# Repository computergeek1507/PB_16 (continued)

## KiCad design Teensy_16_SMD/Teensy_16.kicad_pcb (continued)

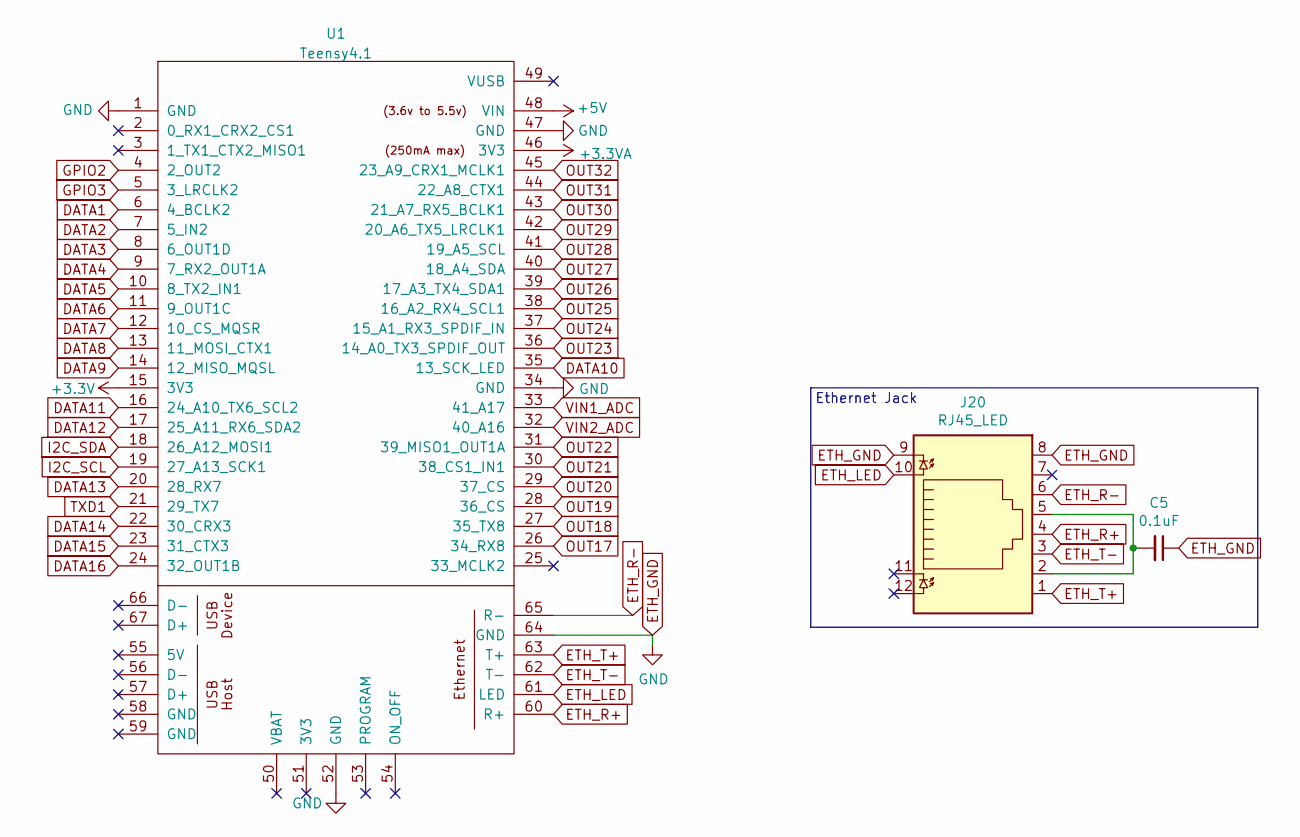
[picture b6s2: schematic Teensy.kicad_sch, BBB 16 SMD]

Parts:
C5: 0.1uF; C_0805_2012Metric; LCSC C49678
J20: RJ45_LED; RJ45_Cetus_J1B1211CCD_Horizontal
U1: Teensy4.1; Teensy41

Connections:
+3.3VA: U1.46 (3V3); also elsewhere on the board
+3V3: U1.15 (3V3); also elsewhere on the board
+5V: U1.48 (VIN); also elsewhere on the board
DATA1: U1.6 (4_BCLK2); also elsewhere on the board
DATA2: U1.7 (5_IN2); also elsewhere on the board
DATA3: U1.8 (6_OUT1D); also elsewhere on the board
DATA4: U1.9 (7_RX2_OUT1A); also elsewhere on the board
DATA5: U1.10 (8_TX2_IN1); also elsewhere on the board
DATA6: U1.11 (9_OUT1C); also elsewhere on the board
DATA7: U1.12 (10_CS_MQSR); also elsewhere on the board
DATA8: U1.13 (11_MOSI_CTX1); also elsewhere on the board
DATA9: U1.14 (12_MISO_MQSL); also elsewhere on the board
DATA10: U1.35 (13_SCK_LED); also elsewhere on the board
DATA11: U1.16 (24_A10_TX6_SCL2); also elsewhere on the board
DATA12: U1.17 (25_A11_RX6_SDA2); also elsewhere on the board
DATA13: U1.20 (28_RX7); also elsewhere on the board
DATA14: U1.22 (30_CRX3); also elsewhere on the board
DATA15: U1.23 (31_CTX3); also elsewhere on the board
DATA16: U1.24 (32_OUT1B); also elsewhere on the board
ETH_GND: C5.1, J20.8, J20.9, U1.1 (GND), U1.34 (GND), U1.47 (GND), U1.52 (GND), U1.64 (GND); also elsewhere on the board
ETH_LED: J20.10, U1.61 (LED)
ETH_R+: J20.4, U1.60 (R+)
ETH_R-: J20.6, U1.65 (R-)
ETH_T+: J20.1, U1.63 (T+)
ETH_T-: J20.3, U1.62 (T-)
GPIO2: U1.4 (2_OUT2); also elsewhere on the board
GPIO3: U1.5 (3_LRCLK2); also elsewhere on the board
I2C_SCL: U1.19 (27_A13_SCK1); also elsewhere on the board
I2C_SDA: U1.18 (26_A12_MOSI1); also elsewhere on the board
unnamed: C5.2, J20.2, J20.5
OUT17: U1.26 (34_RX8); also elsewhere on the board
OUT18: U1.27 (35_TX8); also elsewhere on the board
OUT19: U1.28 (36_CS); also elsewhere on the board
OUT20: U1.29 (37_CS); also elsewhere on the board
OUT21: U1.30 (38_CS1_IN1); also elsewhere on the board
OUT22: U1.31 (39_MISO1_OUT1A); also elsewhere on the board
OUT23: U1.36 (14_A0_TX3_SPDIF_OUT); also elsewhere on the board
OUT24: U1.37 (15_A1_RX3_SPDIF_IN); also elsewhere on the board
OUT25: U1.38 (16_A2_RX4_SCL1); also elsewhere on the board
OUT26: U1.39 (17_A3_TX4_SDA1); also elsewhere on the board
OUT27: U1.40 (18_A4_SDA); also elsewhere on the board
OUT28: U1.41 (19_A5_SCL); also elsewhere on the board
OUT29: U1.42 (20_A6_TX5_LRCLK1); also elsewhere on the board
OUT30: U1.43 (21_A7_RX5_BCLK1); also elsewhere on the board
OUT31: U1.44 (22_A8_CTX1); also elsewhere on the board
OUT32: U1.45 (23_A9_CRX1_MCLK1); also elsewhere on the board
TXD1: U1.21 (29_TX7); also elsewhere on the board
VIN1_ADC: U1.33 (41_A17); also elsewhere on the board
VIN2_ADC: U1.32 (40_A16); also elsewhere on the board

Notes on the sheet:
Ethernet Jack

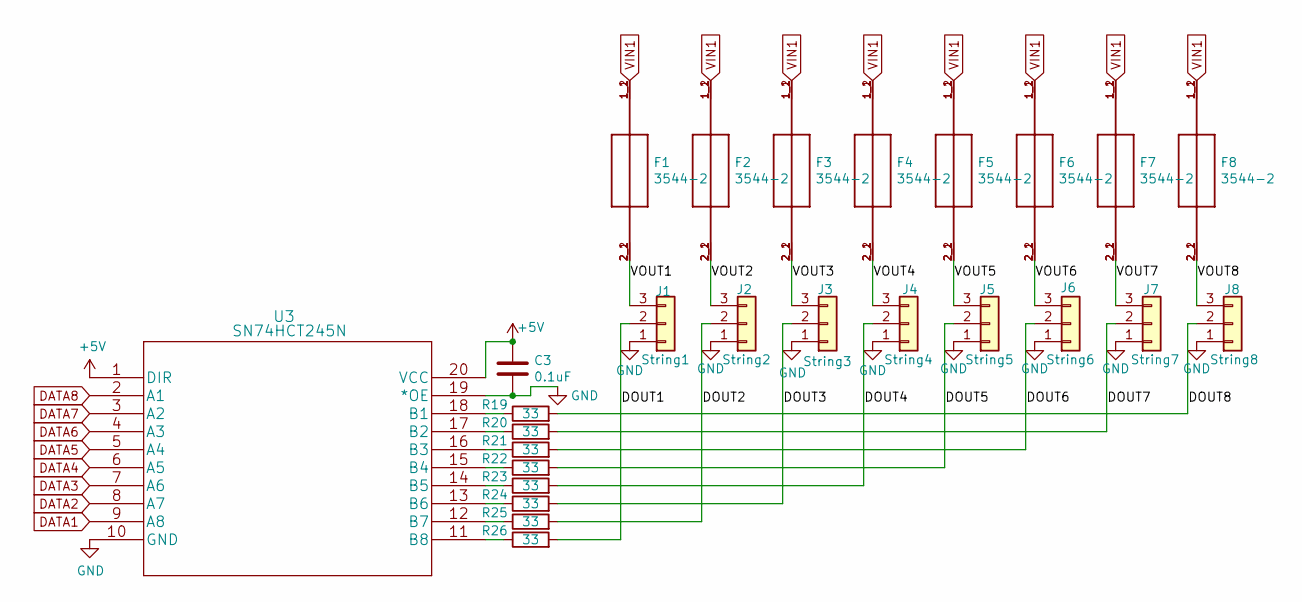
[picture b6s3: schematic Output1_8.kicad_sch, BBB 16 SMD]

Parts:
C3: 0.1uF; C_0603_1608Metric_Pad1.08x0.95mm_HandSolder; MPN CL10B104KB8NNWC; Digi-Key_PN 1276-1935-2-ND
F1, F2, F3, F4, F5, F6, F7, F8: 3544-2; FUSE_3544-2; MPN 3544-2; Digi-Key_PN 36-3544-2-ND
J1: String1; PhoenixContact_MCV_1,5_3-G-3.5_1x03_P3.50mm_Vertical; MPN 1843619/OSTTJ0311530; Digi-Key_PN 277-5737-ND/ED10555-ND
J2: String2; PhoenixContact_MCV_1,5_3-G-3.5_1x03_P3.50mm_Vertical; MPN 1843619/OSTTJ0311530; Digi-Key_PN 277-5737-ND/ED10555-ND
J3: String3; PhoenixContact_MCV_1,5_3-G-3.5_1x03_P3.50mm_Vertical; MPN 1843619/OSTTJ0311530; Digi-Key_PN 277-5737-ND/ED10555-ND
J4: String4; PhoenixContact_MCV_1,5_3-G-3.5_1x03_P3.50mm_Vertical; MPN 1843619/OSTTJ0311530; Digi-Key_PN 277-5737-ND/ED10555-ND
J5: String5; PhoenixContact_MCV_1,5_3-G-3.5_1x03_P3.50mm_Vertical; MPN 1843619/OSTTJ0311530; Digi-Key_PN 277-5737-ND/ED10555-ND
J6: String6; PhoenixContact_MCV_1,5_3-G-3.5_1x03_P3.50mm_Vertical; MPN 1843619/OSTTJ0311530; Digi-Key_PN 277-5737-ND/ED10555-ND
J7: String7; PhoenixContact_MCV_1,5_3-G-3.5_1x03_P3.50mm_Vertical; MPN 1843619/OSTTJ0311530; Digi-Key_PN 277-5737-ND/ED10555-ND
J8: String8; PhoenixContact_MCV_1,5_3-G-3.5_1x03_P3.50mm_Vertical; MPN 1843619/OSTTJ0311530; Digi-Key_PN 277-5737-ND/ED10555-ND
R19, R20, R21, R22, R23, R24, R25, R26: 33; R_0603_1608Metric_Pad0.98x0.95mm_HandSolder; MPN CN34J330CT; LCSC C23140
U3: SN74HCT245N; SN74HCT245NSR; MPN SN74HC245PWR; Digi-Key_PN 296-8279-1-ND

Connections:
+5V: C3.1, U3.1 (DIR), U3.20 (VCC); also elsewhere on the board
/Output 1-8/DOUT1: J1.2, R26.2
/Output 1-8/DOUT2: J2.2, R25.2
/Output 1-8/DOUT3: J3.2, R24.2
/Output 1-8/DOUT4: J4.2, R23.2
/Output 1-8/DOUT5: J5.2, R22.2
/Output 1-8/DOUT6: J6.2, R21.2
/Output 1-8/DOUT7: J7.2, R20.2
/Output 1-8/DOUT8: J8.2, R19.2
/Output 1-8/VOUT1: F1.2_1 (2), F1.2_2 (2), J1.3
/Output 1-8/VOUT2: F2.2_1 (2), F2.2_2 (2), J2.3
/Output 1-8/VOUT3: F3.2_1 (2), F3.2_2 (2), J3.3
/Output 1-8/VOUT4: F4.2_1 (2), F4.2_2 (2), J4.3
/Output 1-8/VOUT5: F5.2_1 (2), F5.2_2 (2), J5.3
/Output 1-8/VOUT6: F6.2_1 (2), F6.2_2 (2), J6.3
/Output 1-8/VOUT7: F7.2_1 (2), F7.2_2 (2), J7.3
/Output 1-8/VOUT8: F8.2_1 (2), F8.2_2 (2), J8.3
DATA1: U3.9 (A8); also elsewhere on the board
DATA2: U3.8 (A7); also elsewhere on the board
DATA3: U3.7 (A6); also elsewhere on the board
DATA4: U3.6 (A5); also elsewhere on the board
DATA5: U3.5 (A4); also elsewhere on the board
DATA6: U3.4 (A3); also elsewhere on the board
DATA7: U3.3 (A2); also elsewhere on the board
DATA8: U3.2 (A1); also elsewhere on the board
ETH_GND: C3.2, J1.1, J2.1, J3.1, J4.1, J5.1, J6.1, J7.1, J8.1, U3.10 (GND), U3.19 (*OE); also elsewhere on the board
unnamed: R19.1, U3.18 (B1)
unnamed: R20.1, U3.17 (B2)
unnamed: R21.1, U3.16 (B3)
unnamed: R22.1, U3.15 (B4)
unnamed: R23.1, U3.14 (B5)
unnamed: R24.1, U3.13 (B6)
unnamed: R25.1, U3.12 (B7)
unnamed: R26.1, U3.11 (B8)
VIN1: F1.1_1 (1), F1.1_2 (1), F2.1_1 (1), F2.1_2 (1), F3.1_1 (1), F3.1_2 (1), F4.1_1 (1), F4.1_2 (1), F5.1_1 (1), F5.1_2 (1), F6.1_1 (1), F6.1_2 (1), F7.1_1 (1), F7.1_2 (1), F8.1_1 (1), F8.1_2 (1); also elsewhere on the board

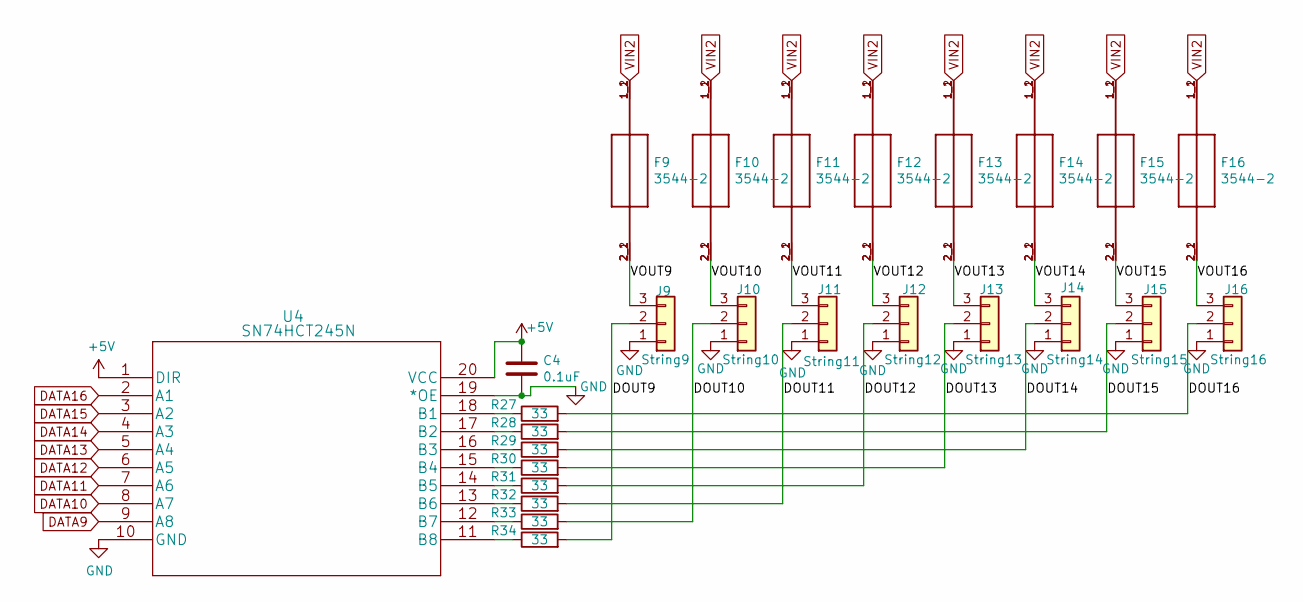
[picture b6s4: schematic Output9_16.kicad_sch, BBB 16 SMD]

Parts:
C4: 0.1uF; C_0603_1608Metric_Pad1.08x0.95mm_HandSolder; MPN CL10B104KB8NNWC; Digi-Key_PN 1276-1935-2-ND
F9, F10, F11, F12, F13, F14, F15, F16: 3544-2; FUSE_3544-2; MPN 3544-2; Digi-Key_PN 36-3544-2-ND
J9: String9; PhoenixContact_MCV_1,5_3-G-3.5_1x03_P3.50mm_Vertical; MPN 1843619/OSTTJ0311530; Digi-Key_PN 277-5737-ND/ED10555-ND
J10: String10; PhoenixContact_MCV_1,5_3-G-3.5_1x03_P3.50mm_Vertical; MPN 1843619/OSTTJ0311530; Digi-Key_PN 277-5737-ND/ED10555-ND
J11: String11; PhoenixContact_MCV_1,5_3-G-3.5_1x03_P3.50mm_Vertical; MPN 1843619/OSTTJ0311530; Digi-Key_PN 277-5737-ND/ED10555-ND
J12: String12; PhoenixContact_MCV_1,5_3-G-3.5_1x03_P3.50mm_Vertical; MPN 1843619/OSTTJ0311530; Digi-Key_PN 277-5737-ND/ED10555-ND
J13: String13; PhoenixContact_MCV_1,5_3-G-3.5_1x03_P3.50mm_Vertical; MPN 1843619/OSTTJ0311530; Digi-Key_PN 277-5737-ND/ED10555-ND
J14: String14; PhoenixContact_MCV_1,5_3-G-3.5_1x03_P3.50mm_Vertical; MPN 1843619/OSTTJ0311530; Digi-Key_PN 277-5737-ND/ED10555-ND
J15: String15; PhoenixContact_MCV_1,5_3-G-3.5_1x03_P3.50mm_Vertical; MPN 1843619/OSTTJ0311530; Digi-Key_PN 277-5737-ND/ED10555-ND
J16: String16; PhoenixContact_MCV_1,5_3-G-3.5_1x03_P3.50mm_Vertical; MPN 1843619/OSTTJ0311530; Digi-Key_PN 277-5737-ND/ED10555-ND
R27, R28, R29, R30, R31, R32, R33, R34: 33; R_0603_1608Metric_Pad0.98x0.95mm_HandSolder; MPN CN34J330CT; LCSC C23140
U4: SN74HCT245N; SN74HCT245NSR; MPN SN74HC245PWR; Digi-Key_PN 296-8279-1-ND

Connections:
+5V: C4.1, U4.1 (DIR), U4.20 (VCC); also elsewhere on the board
/Output 9-16/DOUT9: J9.2, R34.2
/Output 9-16/DOUT10: J10.2, R33.2
/Output 9-16/DOUT11: J11.2, R32.2
/Output 9-16/DOUT12: J12.2, R31.2
/Output 9-16/DOUT13: J13.2, R30.2
/Output 9-16/DOUT14: J14.2, R29.2
/Output 9-16/DOUT15: J15.2, R28.2
/Output 9-16/DOUT16: J16.2, R27.2
/Output 9-16/VOUT9: F9.2_1 (2), F9.2_2 (2), J9.3
/Output 9-16/VOUT10: F10.2_1 (2), F10.2_2 (2), J10.3
/Output 9-16/VOUT11: F11.2_1 (2), F11.2_2 (2), J11.3
/Output 9-16/VOUT12: F12.2_1 (2), F12.2_2 (2), J12.3
/Output 9-16/VOUT13: F13.2_1 (2), F13.2_2 (2), J13.3
/Output 9-16/VOUT14: F14.2_1 (2), F14.2_2 (2), J14.3
/Output 9-16/VOUT15: F15.2_1 (2), F15.2_2 (2), J15.3
/Output 9-16/VOUT16: F16.2_1 (2), F16.2_2 (2), J16.3
DATA9: U4.9 (A8); also elsewhere on the board
DATA10: U4.8 (A7); also elsewhere on the board
DATA11: U4.7 (A6); also elsewhere on the board
DATA12: U4.6 (A5); also elsewhere on the board
DATA13: U4.5 (A4); also elsewhere on the board
DATA14: U4.4 (A3); also elsewhere on the board
DATA15: U4.3 (A2); also elsewhere on the board
DATA16: U4.2 (A1); also elsewhere on the board
ETH_GND: C4.2, J9.1, J10.1, J11.1, J12.1, J13.1, J14.1, J15.1, J16.1, U4.10 (GND), U4.19 (*OE); also elsewhere on the board
unnamed: R27.1, U4.18 (B1)
unnamed: R28.1, U4.17 (B2)
unnamed: R29.1, U4.16 (B3)
unnamed: R30.1, U4.15 (B4)
unnamed: R31.1, U4.14 (B5)
unnamed: R32.1, U4.13 (B6)
unnamed: R33.1, U4.12 (B7)
unnamed: R34.1, U4.11 (B8)
VIN2: F9.1_1 (1), F9.1_2 (1), F10.1_1 (1), F10.1_2 (1), F11.1_1 (1), F11.1_2 (1), F12.1_1 (1), F12.1_2 (1), F13.1_1 (1), F13.1_2 (1), F14.1_1 (1), F14.1_2 (1), F15.1_1 (1), F15.1_2 (1), F16.1_1 (1), F16.1_2 (1); also elsewhere on the board

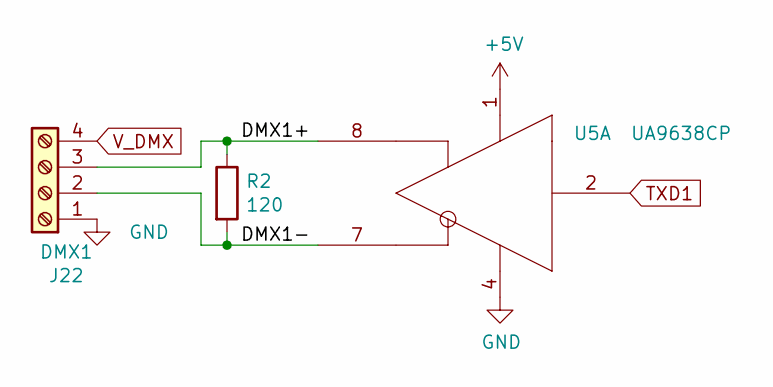
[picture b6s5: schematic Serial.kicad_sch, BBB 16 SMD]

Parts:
J22: DMX1; TerminalBlock_Phoenix_MKDS-1,5-4_1x04_P5.00mm_Horizontal; MPN 1729034; Digi-Key_PN 277-1238-ND
R2: 120; R_0603_1608Metric_Pad0.98x0.95mm_HandSolder; MPN CRGCQ0603F120R; Digi-Key_PN A129677CT-ND
U5: UA9638CP; SOIC-8_3.9x4.9mm_P1.27mm; MPN UA9638CDR; Digi-Key_PN UA9638CP

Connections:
+5V: U5.1 (VCC); also elsewhere on the board
/Serial/DMX1+: J22.3, R2.1, U5.8 (OUTB)
/Serial/DMX1-: J22.2, R2.2, U5.7 (OUTA)
ETH_GND: J22.1, U5.4 (GND); also elsewhere on the board
TXD1: U5.2 (IN); also elsewhere on the board
V_DMX: J22.4; also elsewhere on the board

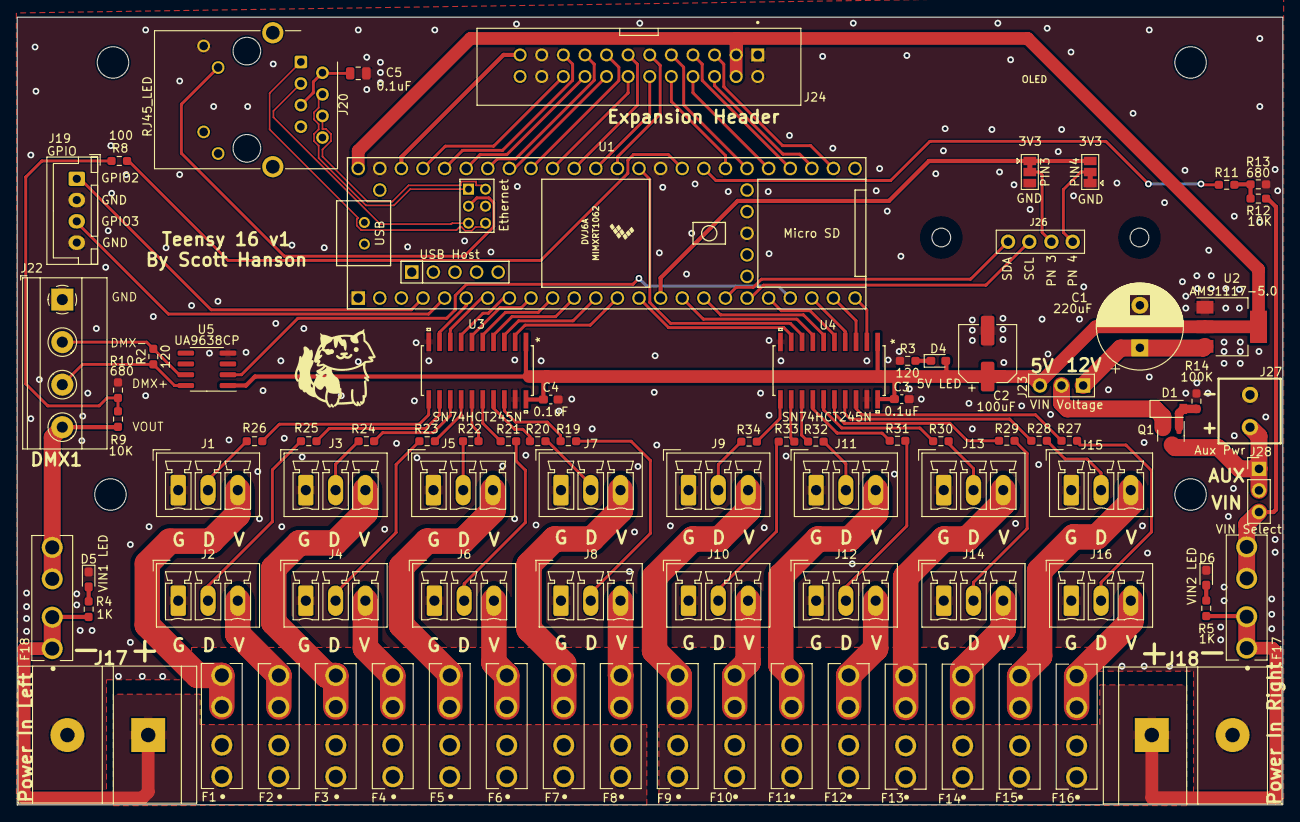
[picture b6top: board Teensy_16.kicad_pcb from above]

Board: 2 copper layers, 148.8 x 92.6 mm, 92 parts (0 on the bottom side), 114 nets.

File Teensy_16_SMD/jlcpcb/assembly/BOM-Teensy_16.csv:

Comment,Designator,Footprint,LCSC
SN74HCT245N,"U3,U4",SN74HCT245NSR,C133641
100uF,C2,CP_Elec_6.3x5.4_Nichicon,C134723
GPIO,J19,JST_XH_B4B-XH-A_1x04_P2.50mm_Vertical,C144395
0.1uF,"C3,C4",C_0603_1608Metric_Pad1.08x0.95mm_HandSolder,C14663
DMP3056L,Q1,SOT-23,C150724
Zener 10V,D1,D_SOD-123,C173431
DMX1,J22,"TerminalBlock_Phoenix_MKDS-1,5-4_1x04_P5.00mm_Horizontal",C192769
String1,"J1,J10,J11,J12,J13,J14,J15,J16,J2,J3,J4,J5,J6,J7,J8,J9","PhoenixContact_MCV_1,5_3-G-3.5_1x03_P3.50mm_Vertical",C192778
1K,"R4,R5",R_0603_1608Metric_Pad0.98x0.95mm_HandSolder,C21190
Expansion Header,J24,OST_302-S241,C221083
OLED,J26,OLED-SSD1306-128X64-I2C-THT,C225501
100,"R11,R8",R_0603_1608Metric_Pad0.98x0.95mm_HandSolder,C22775
120,"R2,R3",R_0603_1608Metric_Pad0.98x0.95mm_HandSolder,C22787
5V LED,"D4,D5,D6,F1,F10,F11,F2,F3,F4,F5,F6,F7,F8,F9",LED_0603_1608Metric_Pad1.05x0.95mm_HandSolder,C2297
33,"R19,R20,R21,R22,R23,R24,R25,R26,R27,R28,R29,R30,R31,R32,R33,R34",R_0603_1608Metric_Pad0.98x0.95mm_HandSolder,C23140
680,"R10,R13",R_0603_1608Metric_Pad0.98x0.95mm_HandSolder,C23228
100K,R14,R_0603_1608Metric_Pad0.98x0.95mm_HandSolder,C25803
10K,"R12,R9",R_0603_1608Metric_Pad0.98x0.95mm_HandSolder,C25804
UA9638CP,U5,SOIC-8_3.9x4.9mm_P1.27mm,C435812
VIN Voltage,"J23,J28",PinHeader_1x03_P2.54mm_Vertical,C49257
3544-2,"F12,F13,F14,F15,F16,F17,F18",FUSE_3544-2,C492610
0.1uF,C5,C_0805_2012Metric,C49678
AMS1117-5.0,U2,SOT-223-3_TabPin2,C6187
Aux Pwr,J27,PHOENIX_MKDS1_2-3.81,C69811
Power In Left,"J17,J18",BARRIER_BLOCK_1ROW_2POS_P9.5MM,C707421
220uF,C1,CP_Radial_D10.0mm_P5.00mm,C88784
MountingHole,H4,MountingHole_3.7mm,
MountingHole,H2,MountingHole_3.7mm,
RJ45_LED,J20,RJ45_Cetus_J1B1211CCD_Horizontal,
JUMPER,PIN4,SolderJumper-3_P1.3mm_Bridged12_Pad1.0x1.5mm,
Jumper,PIN3,SolderJumper-3_P1.3mm_Bridged12_Pad1.0x1.5mm,
Teensy4.1,U1,Teensy41,
MountingHole,H1,MountingHole_3.7mm,
MountingHole,H5,MountingHole_3.7mm,

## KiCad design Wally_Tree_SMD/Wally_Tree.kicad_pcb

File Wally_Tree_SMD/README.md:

# Copyright and Disclaimer
Copyright: Scott Hanson

This documentation describes Open Hardware and is licensed under the CERN Open Hardware License Version 2 - Strongly Reciprocal. (CERN-OHL-S)

You may redistribute and modify this documentation under the terms of the CERN OHL-S-v2 (https://ohwr.org/cern_ohl_s_v2.txt). This documentation is distributed WITHOUT ANY EXPRESS OR IMPLIED WARRANTY, INCLUDING OF MERCHANTABILITY, SATISFACTORY QUALITY AND FITNESS FOR A PARTICULAR PURPOSE. Please see the CERN OHL v2-S for applicable conditions

**Under CERN OHL-S-v2, derivative work must be publicly released as defined in subsection 3.3**

# Wally Tree Driver

The "Wally Tree Driver" is a Differental Reciver board designed to control at 5" Holiday Time RGB Tree from Walmart[Link](https://www.walmart.com/ip/Holiday-Time-5-Rgb-Color-Changing-Pixel-Tree/908536686). All the design files are open source and available on github.

To order PCBs upload the "GERBER-Wally_Tree.zip" file in the "jlcpcb\gerber" folder. Enable the SMD service, 'BOM-Wally_Tree.csv' is the SMD BOM and 'POS-Wally_Tree.csv' is the SMD CPL position file.

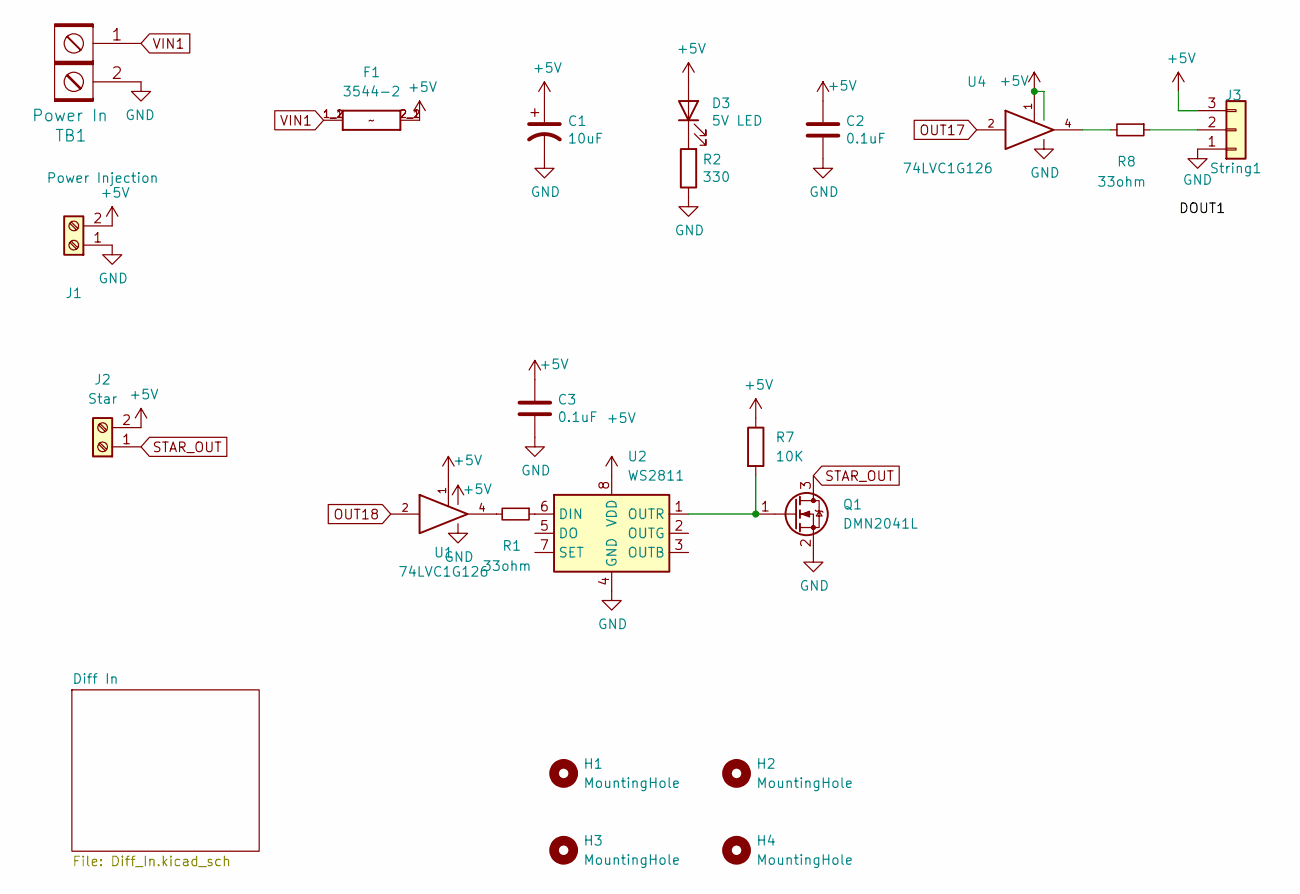
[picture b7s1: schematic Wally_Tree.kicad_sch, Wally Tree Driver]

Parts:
C1: 10uF; C_0805_2012Metric_Pad1.18x1.45mm_HandSolder; MPN GRM21BR61E106KA73L; Digi-Key_PN 490-5523-1-ND
C2, C3: 0.1uF; C_0402_1005Metric; MPN 0402B104K160CT; Digi-Key_PN 1292-1630-1-ND
D3: 5V LED; LED_0603_1608Metric_Pad1.05x0.95mm_HandSolder; MPN 150080RS75000; Digi-Key_PN 732-4984-1-ND
F1: 3544-2; FUSE_3544-2; MPN 3544-2; Digi-Key_PN 36-3544-2-ND
H1, H2, H3, H4: MountingHole; MountingHole_3.7mm
J1: Power Injection; TerminalBlock_Phoenix_MKDS-1,5-2_1x02_P5.00mm_Horizontal; LCSC_PN C8404
J2: Star; TerminalBlock_Phoenix_MKDS-1,5-2_1x02_P5.00mm_Horizontal; LCSC_PN C8404
J3: String1; PhoenixContact_MCV_3.81mm_3.5mm_1x03_Vertical; MPN 1843619/OSTTJ0311530; Digi-Key_PN 277-5737-ND/ED10555-ND
Q1: DMN2041L; SOT-23; LCSC_PN C154903
R1, R8: 33ohm; R_0603_1608Metric_Pad0.98x0.95mm_HandSolder; MPN RC0603JR-0733RL; LCSC_PN C23140
R2: 330; R_0603_1608Metric_Pad0.98x0.95mm_HandSolder; MPN CRGCQ0603F120R; Digi-Key_PN A129677CT-ND
R7: 10K; R_0603_1608Metric_Pad0.98x0.95mm_HandSolder; LCSC_PN C25804
TB1: Power In; BARRIER_BLOCK_1ROW_2POS; MPN 4DB-P108-02; Digi-Key_PN A98472-ND
U1, U4: 74LVC1G126; TSOP-5_1.65x3.05mm_P0.95mm; LCSC_PN C7834
U2: WS2811; SOP-8_3.76x4.96mm_P1.27mm; LCSC_PN C114581

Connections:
+5V: C1.1, C2.1, C3.1, D3.2 (A), F1.2_1 (2), F1.2_2 (2), J1.2, J2.2, J3.3, R7.1, U1.1, U1.5 (VCC), U2.8 (VDD), U4.1, U4.5 (VCC); also elsewhere on the board
GND: C1.2, C2.2, C3.2, J1.1, J3.1, Q1.2 (S), R2.1, TB1.2, U1.3 (GND), U2.4 (GND), U4.3 (GND); also elsewhere on the board
unnamed: D3.1 (K), R2.2
unnamed: J3.2, R8.1
unnamed: Q1.1 (G), R7.2, U2.1 (OUTR)
unnamed: R1.1, U2.6 (DIN)
unnamed: R1.2, U1.4
unnamed: R8.2, U4.4
OUT17: U4.2; also elsewhere on the board
OUT18: U1.2; also elsewhere on the board
STAR_OUT: J2.1, Q1.3 (D)
VIN1: F1.1_1 (1), F1.1_2 (1), TB1.1

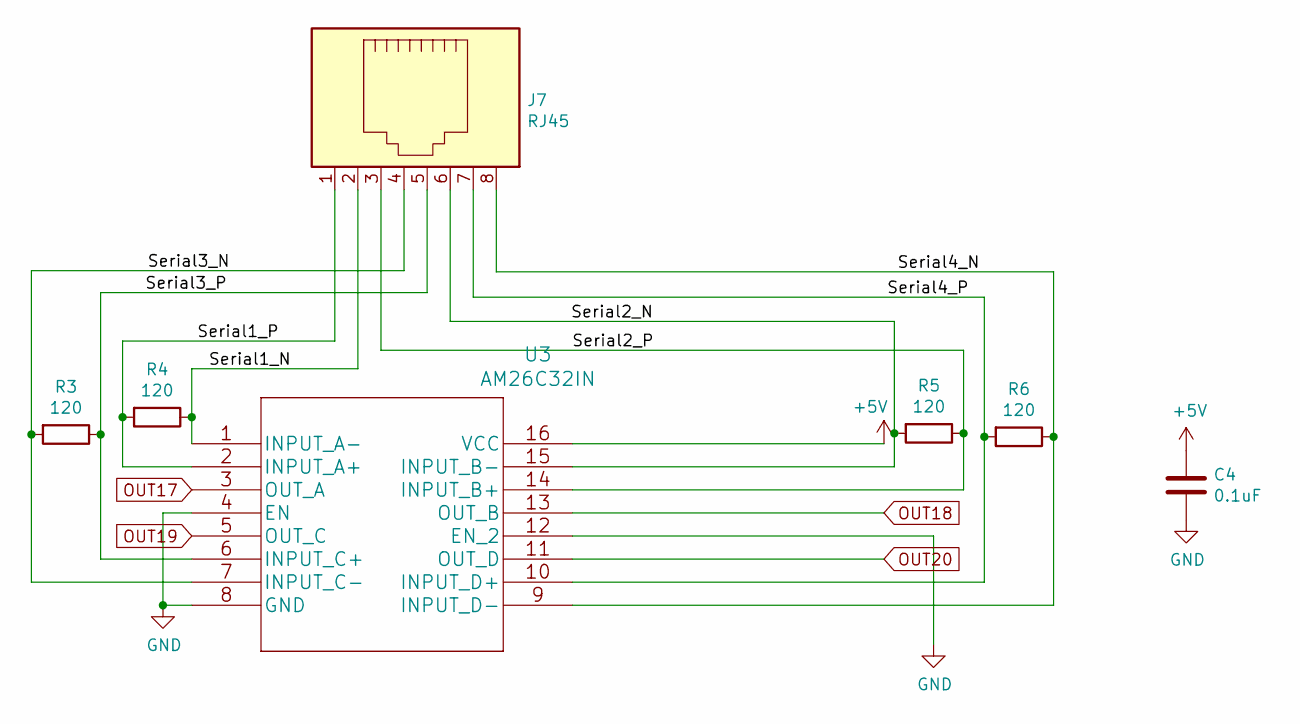
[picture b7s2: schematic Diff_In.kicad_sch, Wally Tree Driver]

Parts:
C4: 0.1uF; C_0402_1005Metric; MPN 0402B104K160CT; Digi-Key_PN 1292-1630-1-ND
J7: RJ45; RJ45_Amphenol_54602-x08_Horizontal; MPN A-2014-2-4-R; Digi-Key_PN AE10392-ND
R3, R4, R5, R6: 120; R_0603_1608Metric_Pad0.98x0.95mm_HandSolder; MPN CRGCQ0603F120R; LCSC_PN C22787
U3: AM26C32IN; SOIC-16_3.9x9.9mm_P1.27mm; MPN AM26C32INSR; Digi-Key_PN 296-37322-1-ND

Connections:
+5V: C4.1, U3.16 (VCC); also elsewhere on the board
/Diff In/Serial1_N: J7.2, R4.1, U3.1 (INPUT_A-)
/Diff In/Serial1_P: J7.1, R4.2, U3.2 (INPUT_A+)
/Diff In/Serial2_N: J7.6, R5.2, U3.15 (INPUT_B-)
/Diff In/Serial2_P: J7.3, R5.1, U3.14 (INPUT_B+)
/Diff In/Serial3_N: J7.4, R3.2, U3.7 (INPUT_C-)
/Diff In/Serial3_P: J7.5, R3.1, U3.6 (INPUT_C+)
/Diff In/Serial4_N: J7.8, R6.1, U3.9 (INPUT_D-)
/Diff In/Serial4_P: J7.7, R6.2, U3.10 (INPUT_D+)
GND: C4.2, U3.4 (EN), U3.8 (GND), U3.12 (EN_2); also elsewhere on the board
OUT17: U3.3 (OUT_A); also elsewhere on the board
OUT18: U3.13 (OUT_B); also elsewhere on the board
OUT19: U3.5 (OUT_C)
OUT20: U3.11 (OUT_D)

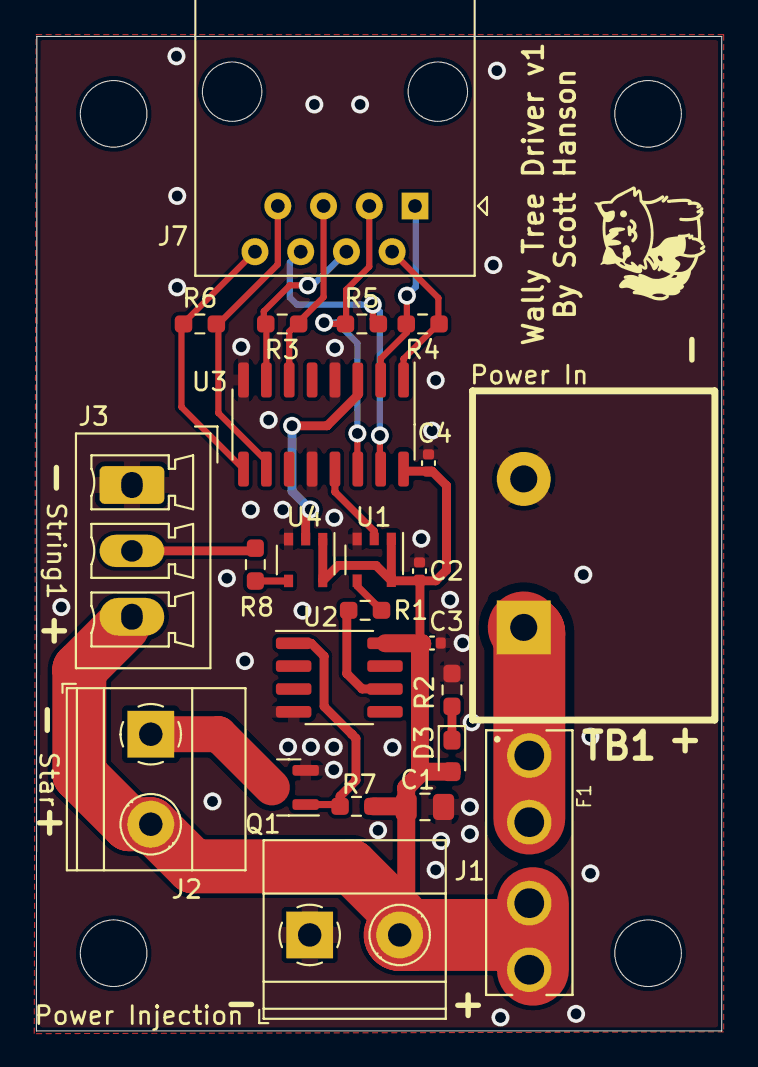
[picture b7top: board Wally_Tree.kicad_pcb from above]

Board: 2 copper layers, 38.1 x 55.2 mm, 28 parts (0 on the bottom side), 20 nets.

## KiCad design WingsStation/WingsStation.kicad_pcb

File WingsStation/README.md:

# Copyright and Disclaimer
Copyright: Scott Hanson

This documentation describes Open Hardware and is licensed under the CERN Open Hardware License Version 2 - Strongly Reciprocal. (CERN-OHL-S)

You may redistribute and modify this documentation under the terms of the CERN OHL-S-v2 (https://ohwr.org/cern_ohl_s_v2.txt). This documentation is distributed WITHOUT ANY EXPRESS OR IMPLIED WARRANTY, INCLUDING OF MERCHANTABILITY, SATISFACTORY QUALITY AND FITNESS FOR A PARTICULAR PURPOSE. Please see the CERN OHL v2-S for applicable conditions

**Under CERN OHL-S-v2, derivative work must be publicly released as defined in subsection 3.3**

# Button Station SMD

The "Button Station SMD" is a 4 port Selfy Station that reacts to Button Presses. The Firmware is a work in progress. This design is surface mount based and is harder to solder. All the design files are open source and available on github.

**WIP** Work in progress, firmware and PCB may change.

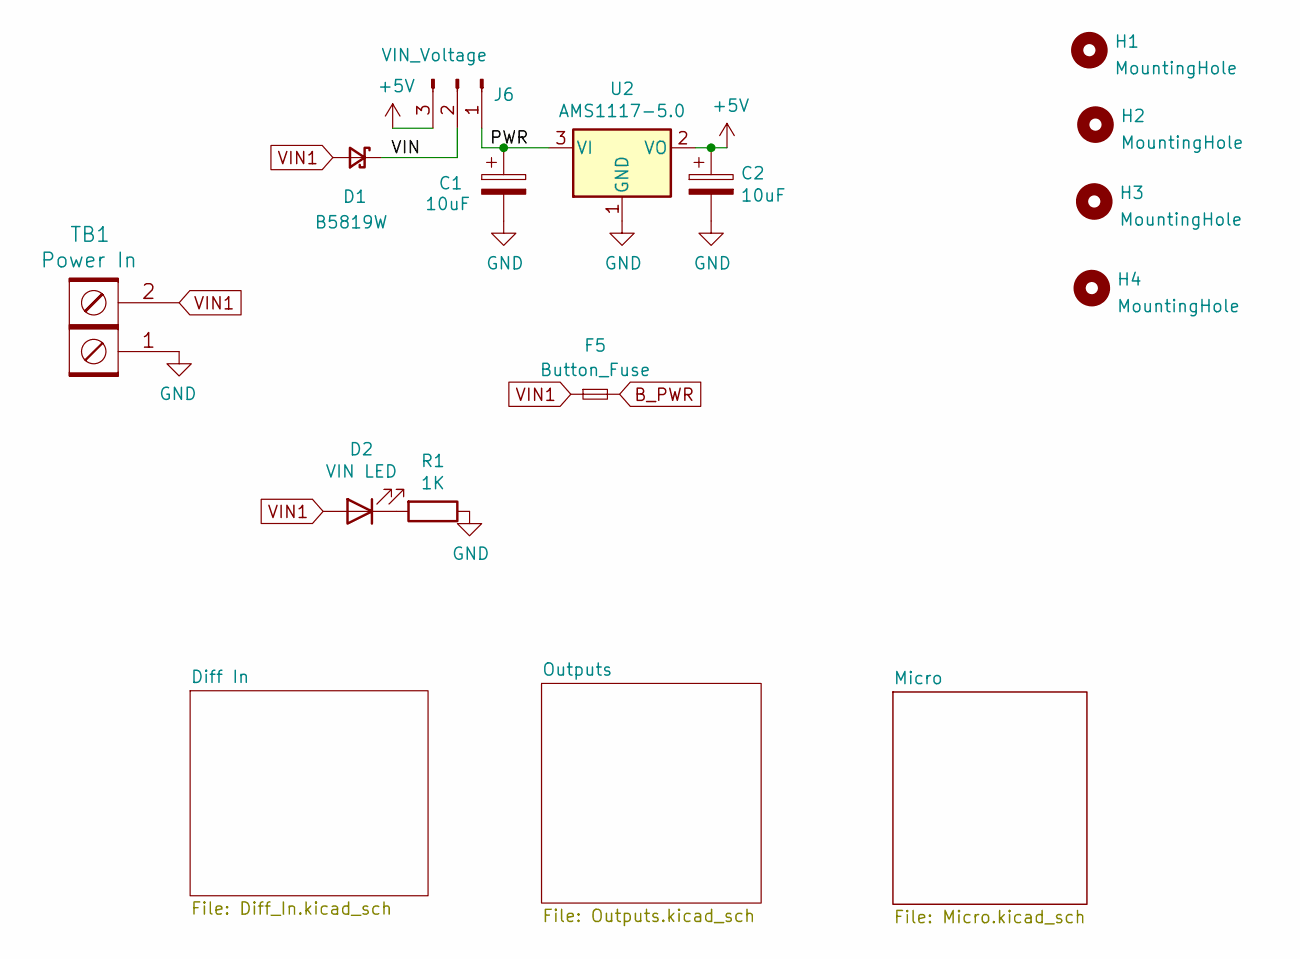
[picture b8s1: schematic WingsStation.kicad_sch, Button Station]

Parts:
C1, C2: 10uF; C_0805_2012Metric_Pad1.18x1.45mm_HandSolder; MPN GRM21BR61E106KA73L; Digi-Key_PN 490-5523-1-ND
D1: B5819W; D_SOD-123; MPN B5819W-TP; LCSC_PN C8598
D2: VIN LED; LED_0603_1608Metric_Pad1.05x0.95mm_HandSolder; MPN 150080RS75000; Digi-Key_PN 732-4984-1-ND
F5: Button_Fuse; Fuse_0805_2012Metric; LCSC C261938
H1, H2, H3, H4: MountingHole; MountingHole_3.7mm
J6: VIN_Voltage; PinHeader_1x03_P2.54mm_Vertical; MPN 61300311121; Digi-Key_PN 732-5316-ND
R1: 1K; R_0603_1608Metric_Pad0.98x0.95mm_HandSolder; MPN RC0603FR-071KL; Digi-Key_PN 311-1.00KHRCT-ND
TB1: Power In; BARRIER_BLOCK_1ROW_2POS; MPN 4DB-P108-02; Digi-Key_PN A98472-ND
U2: AMS1117-5.0; SOT-223-3_TabPin2; MPN LM1117MPX-50NOPB; LCSC_PN C6187

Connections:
+5V: C2.1, J6.3, U2.2 (VO); also elsewhere on the board
/PWR: C1.1, J6.1, U2.3 (VI)
/VIN: D1.1 (K), J6.2
B_PWR: F5.2; also elsewhere on the board
GND: C1.2, C2.2, R1.1, TB1.1, U2.1 (GND); also elsewhere on the board
unnamed: D2.1 (K), R1.2
VIN1: D1.2 (A), D2.2 (A), F5.1, TB1.2; also elsewhere on the board

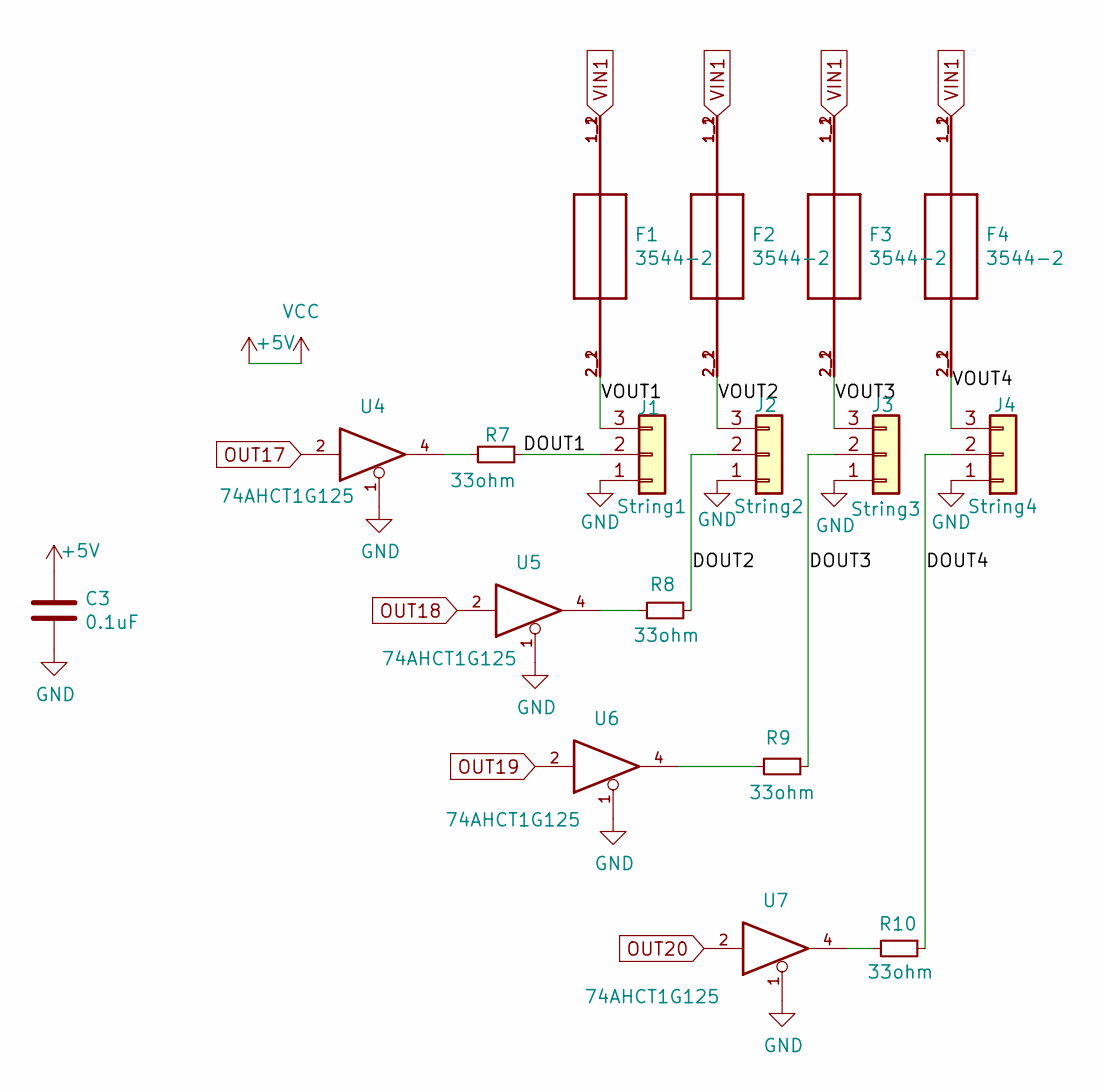
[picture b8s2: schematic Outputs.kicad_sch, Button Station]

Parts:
C3: 0.1uF; C_0603_1608Metric_Pad1.08x0.95mm_HandSolder; MPN CL10B104KB8NNWC; Digi-Key_PN 1276-1935-2-ND
F1, F2, F3, F4: 3544-2; FUSE_3544-2; MPN 3544-2; Digi-Key_PN 36-3544-2-ND
J1: String1; PhoenixContact_MCV_1,5_3-G-3.5_1x03_P3.50mm_Vertical; MPN 1843619/OSTTJ0311530; Digi-Key_PN 277-5737-ND/ED10555-ND
J2: String2; PhoenixContact_MCV_1,5_3-G-3.5_1x03_P3.50mm_Vertical; MPN 1843619/OSTTJ0311530; Digi-Key_PN 277-5737-ND/ED10555-ND
J3: String3; PhoenixContact_MCV_1,5_3-G-3.5_1x03_P3.50mm_Vertical; MPN 1843619/OSTTJ0311530; Digi-Key_PN 277-5737-ND/ED10555-ND
J4: String4; PhoenixContact_MCV_1,5_3-G-3.5_1x03_P3.50mm_Vertical; MPN 1843619/OSTTJ0311530; Digi-Key_PN 277-5737-ND/ED10555-ND
R7, R8, R9, R10: 33ohm; R_0603_1608Metric_Pad0.98x0.95mm_HandSolder; MPN RC0603JR-0733RL; LCSC_PN C23140
U4, U5, U6, U7: 74AHCT1G125; TSOP-5_1.65x3.05mm_P0.95mm; MPN 74AHCT1G125W5-7; Digi-Key_PN 74AHCT1G125W5-7DICT-ND

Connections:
+5V: C3.1, U4.5 (VCC), U5.5 (VCC), U6.5 (VCC), U7.5 (VCC); also elsewhere on the board
/Outputs/DOUT1: J1.2, R7.1
/Outputs/DOUT2: J2.2, R8.1
/Outputs/DOUT3: J3.2, R9.1
/Outputs/DOUT4: J4.2, R10.1
/Outputs/VOUT1: F1.2_1 (2), F1.2_2 (2), J1.3
/Outputs/VOUT2: F2.2_1 (2), F2.2_2 (2), J2.3
/Outputs/VOUT3: F3.2_1 (2), F3.2_2 (2), J3.3
/Outputs/VOUT4: F4.2_1 (2), F4.2_2 (2), J4.3
GND: C3.2, J1.1, J2.1, J3.1, J4.1, U4.1, U4.3 (GND), U5.1, U5.3 (GND), U6.1, U6.3 (GND), U7.1, U7.3 (GND); also elsewhere on the board
unnamed: R7.2, U4.4
unnamed: R8.2, U5.4
unnamed: R9.2, U6.4
unnamed: R10.2, U7.4
OUT17: U4.2; also elsewhere on the board
OUT18: U5.2; also elsewhere on the board
OUT19: U6.2; also elsewhere on the board
OUT20: U7.2; also elsewhere on the board
VIN1: F1.1_1 (1), F1.1_2 (1), F2.1_1 (1), F2.1_2 (1), F3.1_1 (1), F3.1_2 (1), F4.1_1 (1), F4.1_2 (1); also elsewhere on the board

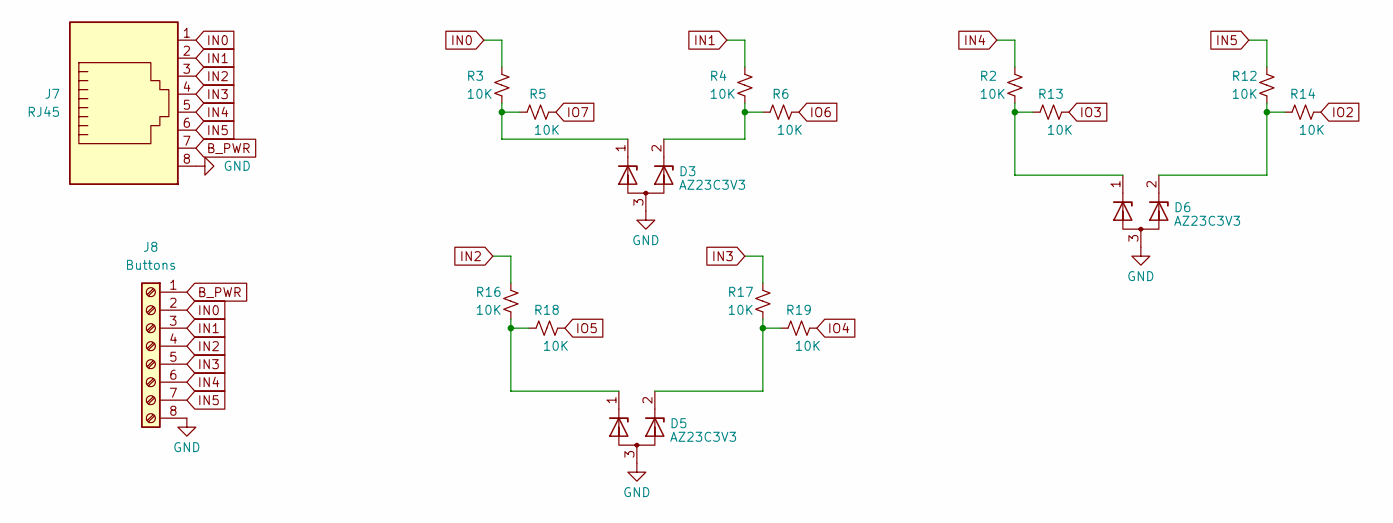
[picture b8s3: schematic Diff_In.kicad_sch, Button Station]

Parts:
D3, D5, D6: AZ23C3V3; SOT-23; MPN AZ23C3V3-E3-08; Digi-Key_PN AZ23C3V3-E3-08GICT-ND
J7: RJ45; RJ45_Amphenol_54602-x08_Horizontal; MPN A-2014-2-4-R; Digi-Key_PN AE10392-ND
J8: Buttons; PhoenixContact_MCV_1,5_8-G-5.08_1x08_P5.08mm_Vertical
R2, R3, R4, R5, R6, R12, R13, R14, R16, R17, R18, R19: 10K; R_0603_1608Metric; MPN RNCP0603FTD10K0; Digi-Key_PN RNCP0603FTD10K0CT-ND

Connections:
B_PWR: J7.7, J8.1; also elsewhere on the board
GND: D3.3 (A), D5.3 (A), D6.3 (A), J7.8, J8.8; also elsewhere on the board
IN0: J7.1, J8.2, R3.1
IN1: J7.2, J8.3, R4.1
IN2: J7.3, J8.4, R16.1
IN3: J7.4, J8.5, R17.1
IN4: J7.5, J8.6, R2.1
IN5: J7.6, J8.7, R12.1
IO2: R14.2; also elsewhere on the board
IO3: R13.2; also elsewhere on the board
IO4: R19.2; also elsewhere on the board
IO5: R18.2; also elsewhere on the board
IO6: R6.2; also elsewhere on the board
IO7: R5.2; also elsewhere on the board
unnamed: D3.1 (K), R3.2, R5.1
unnamed: D3.2 (K), R4.2, R6.1
unnamed: D5.1 (K), R16.2, R18.1
unnamed: D5.2 (K), R17.2, R19.1
unnamed: D6.1 (K), R2.2, R13.1
unnamed: D6.2 (K), R12.2, R14.1
